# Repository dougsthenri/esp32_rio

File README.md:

# ESP32 Remote I/O

A low-cost industrial remote input/output device based on the ESP32-S3 SoC from Espressif.

## Features

* **WiFi Connectivity:** Connects to an existing WiFi network using configuration read from non-volatile storage. External antenna.
* **Digital Inputs (DI):** Ten 24 V digital, sink type, inputs.
* **Digital Outputs (DQ):** Twenty 24 V digital, sink type, outputs.
* **Output Enable (OE) Button:** A push button to globally enable/disable digital outputs.
* **Status LED:** Steady on when digital outputs are enabled. Blinks Morse code for the letter W when disconnected from WiFi network.
* **USB Console:** A command-line interface over USB Serial/JTAG for runtime configuration (e.g., WiFi setup) and debugging.
* **Reset Button:** For manually restarting the board.
* **Power Input:** 24 V, 267 mA (max.).

---
*For any issues or contributions, please refer to the project's [GitHub repository](https://github.com/dougsthenri/esp32_rio.git).*

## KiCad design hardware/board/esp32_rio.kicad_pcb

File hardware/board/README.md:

# esp32_rio
PCB project for a low-cost industrial remote I/O device based on the ESP32-S3 SoC from Espressif.
Proudly made using KiCad 9.0.

---
*For any issues or contributions, please refer to the project's [GitHub repository](https://github.com/dougsthenri/esp32_rio.git).*

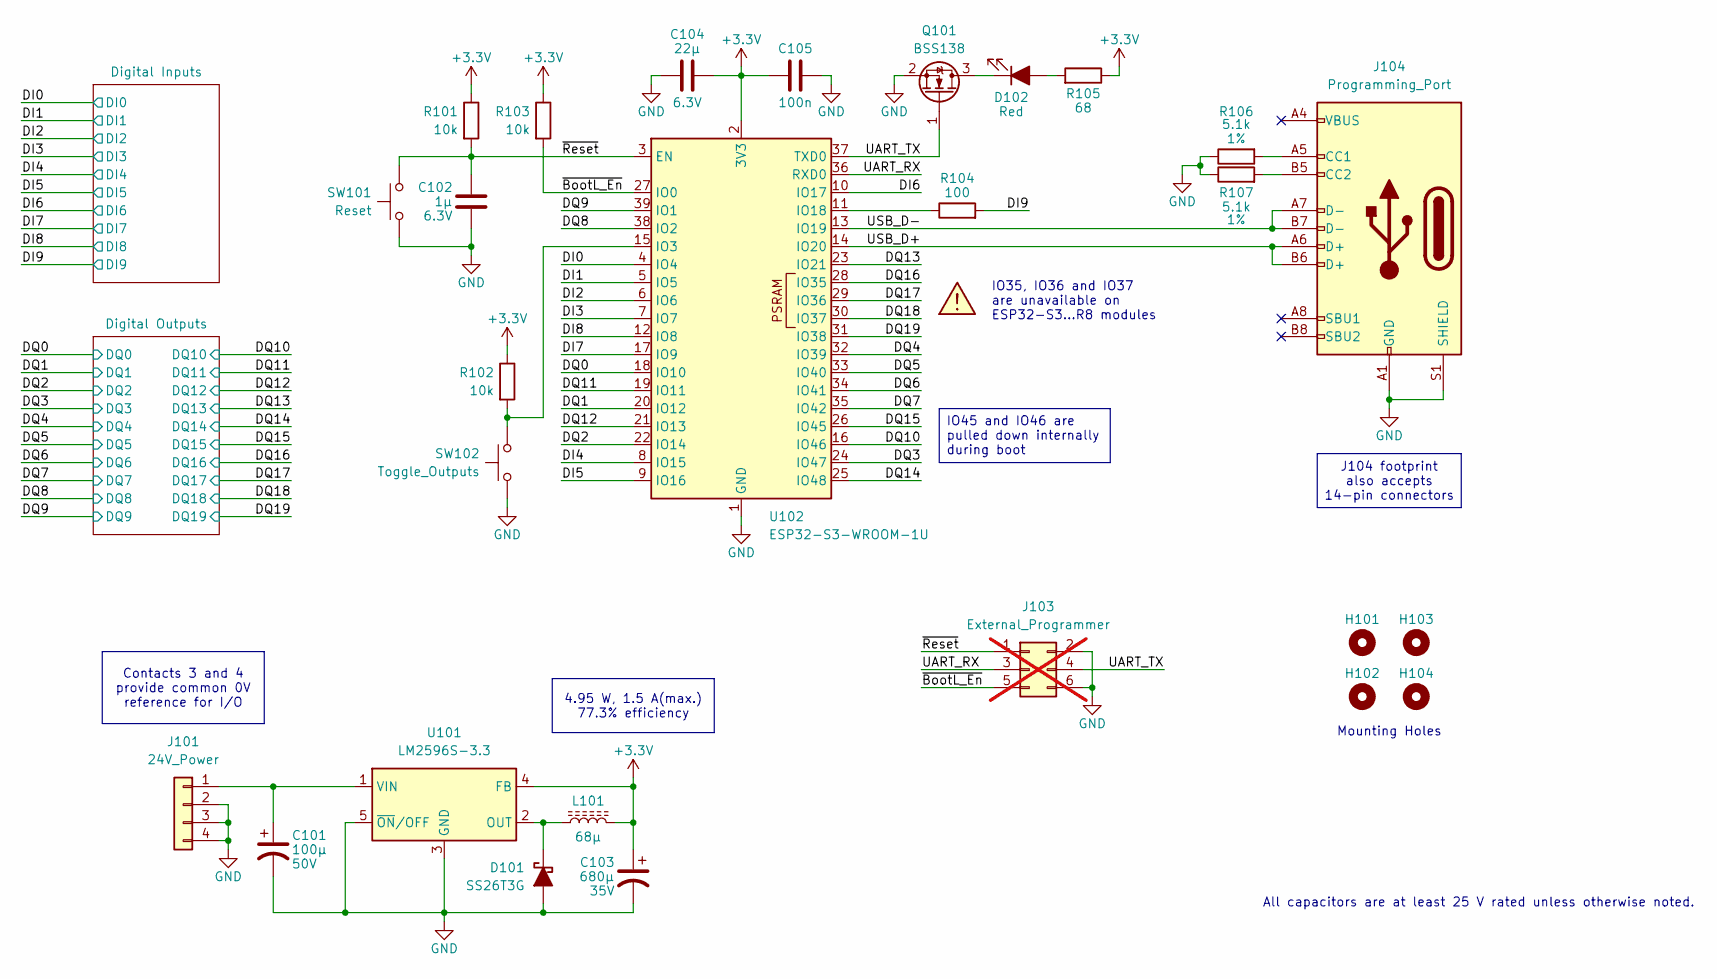
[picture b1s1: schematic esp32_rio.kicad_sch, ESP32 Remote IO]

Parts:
C101: 100µ; C_Elec_10x10.2; Voltage 50V; Part# EEHZC1H101P
C102: 1µ; C_0603_1608Metric; Voltage 6.3V; Part# CL10B105KQ8NNNC
C103: 680µ; C_Elec_10x10.2; Voltage 35V; Part# EEEFK1V331P
C104: 22µ; C_0805_2012Metric; Voltage 6.3V; Part# GRM21BZ70J226ME44L
C105: 100n; C_0603_1608Metric; Part# CC0603JRX7R9BB104
D101: SS26T3G; D_SMB; Part# SS26T3G
D102: Red; LED_Rectangular_W5.0mm_H2.0mm; Part# L-403SRD
H101, H102, H103, H104: MountingHole; MountingHole_2.1mm
J101: 24V_Power; Kefa_KF142V-5.08-4P; Part# KF142V-5.08-4P
J103: External_Programmer; PinHeader_2x03_P2.54mm_Vertical; not fitted
J104: Programming_Port; CUI_UJ20-C-V-C-3-SMT-TR; Part# GT-USB-7035D
L101: 68µ; L_Vishay_IHLP-6767; Part# IHLP6767GZER680M11
Q101: BSS138; SOT-23; Part# BSS138-7-F
R101, R102, R103: 10k; R_0603_1608Metric; Part# RC0603FR-0710KL
R104: 100; R_0603_1608Metric; Part# AC0603FR-07100RL
R105: 68; R_0603_1608Metric; Part# RC0603FR-0768RL
R106, R107: 5.1k; R_0603_1608Metric; Tolerance 1%; Part# RC0603FR-075K1L
SW101: Reset; SW_SPST_PTS645; Part# PTS645SH95SMTR92LFS
SW102: Toggle_Outputs; SW_SPST_PTS645; Part# PTS645SH95SMTR92LFS
U101: LM2596S-3.3; TO-263-5_TabPin3; Part# LM2596SX-3.3/NOPB
U102: ESP32-S3-WROOM-1U; Part# ESP32-S3-WROOM-1U-N16R2

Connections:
+3.3V: C103.1, C104.1, C105.2, L101.2, R101.1, R102.1, R103.1, R105.1, U101.4 (FB), U102.2 (3V3); also elsewhere on the board
/DI0: U102.4 (IO4); also elsewhere on the board
/DI1: U102.5 (IO5); also elsewhere on the board
/DI2: U102.6 (IO6); also elsewhere on the board
/DI3: U102.7 (IO7); also elsewhere on the board
/DI4: U102.8 (IO15); also elsewhere on the board
/DI5: U102.9 (IO16); also elsewhere on the board
/DI6: U102.10 (IO17); also elsewhere on the board
/DI7: U102.17 (IO9); also elsewhere on the board
/DI8: U102.12 (IO8); also elsewhere on the board
/DI9: R104.2; also elsewhere on the board
/DQ0: U102.18 (IO10); also elsewhere on the board
/DQ1: U102.20 (IO12); also elsewhere on the board
/DQ2: U102.22 (IO14); also elsewhere on the board
/DQ3: U102.24 (IO47); also elsewhere on the board
/DQ4: U102.32 (IO39); also elsewhere on the board
/DQ5: U102.33 (IO40); also elsewhere on the board
/DQ6: U102.34 (IO41); also elsewhere on the board
/DQ7: U102.35 (IO42); also elsewhere on the board
/DQ8: U102.38 (IO2); also elsewhere on the board
/DQ9: U102.39 (IO1); also elsewhere on the board
/DQ10: U102.16 (IO46); also elsewhere on the board
/DQ11: U102.19 (IO11); also elsewhere on the board
/DQ12: U102.21 (IO13); also elsewhere on the board
/DQ13: U102.23 (IO21); also elsewhere on the board
/DQ14: U102.25 (IO48); also elsewhere on the board
/DQ15: U102.26 (IO45); also elsewhere on the board
/DQ16: U102.28 (IO35); also elsewhere on the board
/DQ17: U102.29 (IO36); also elsewhere on the board
/DQ18: U102.30 (IO37); also elsewhere on the board
/DQ19: U102.31 (IO38); also elsewhere on the board
/UART_RX: J103.3, U102.36 (RXD0)
/UART_TX: J103.4, Q101.1 (G), U102.37 (TXD0)
/USB_D+: J104.A6 (D+), J104.B6 (D+), U102.14 (IO20)
/USB_D-: J104.A7 (D-), J104.B7 (D-), U102.13 (IO19)
/~BootL_En: J103.5, R103.2, U102.27 (IO0)
/~Reset: C102.1, J103.1, R101.2, SW101.2, U102.3 (EN)
GND: C101.2, C102.2, C103.2, C104.2, C105.1, D101.2 (A), J101.2, J101.3, J101.4, J103.2, J103.6, J104.A1 (GND), J104.A12 (GND), J104.B1 (GND), J104.B12 (GND), J104.S1 (SHIELD), Q101.2 (S), R106.1, R107.1, SW101.1, SW102.1, U101.3 (GND), U101.5 (~ON/OFF), U102.1 (GND), U102.40 (GND), U102.41 (GND); also elsewhere on the board
unnamed: D101.1 (K), L101.1, U101.2 (OUT)
unnamed: D102.2 (A), R105.2
unnamed: D102.1 (K), Q101.3 (D)
unnamed: C101.1, J101.1, U101.1 (VIN)
unnamed: J104.A5 (CC1), R106.2
unnamed: J104.B5 (CC2), R107.2
unnamed: R102.2, SW102.2, U102.15 (IO3)
unnamed: R104.1, U102.11 (IO18)

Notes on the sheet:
Mounting Holes
All capacitors are at least 25 V rated unless otherwise noted.
J104 footprint also accepts 14-pin connectors
4.95 W, 1.5 A(max.) 77.3% efficiency
IO35, IO36 and IO37 are unavailable on ESP32-S3...R8 modules
Contacts 3 and 4 provide common 0V reference for I/O
IO45 and IO46 are pulled down internally during boot

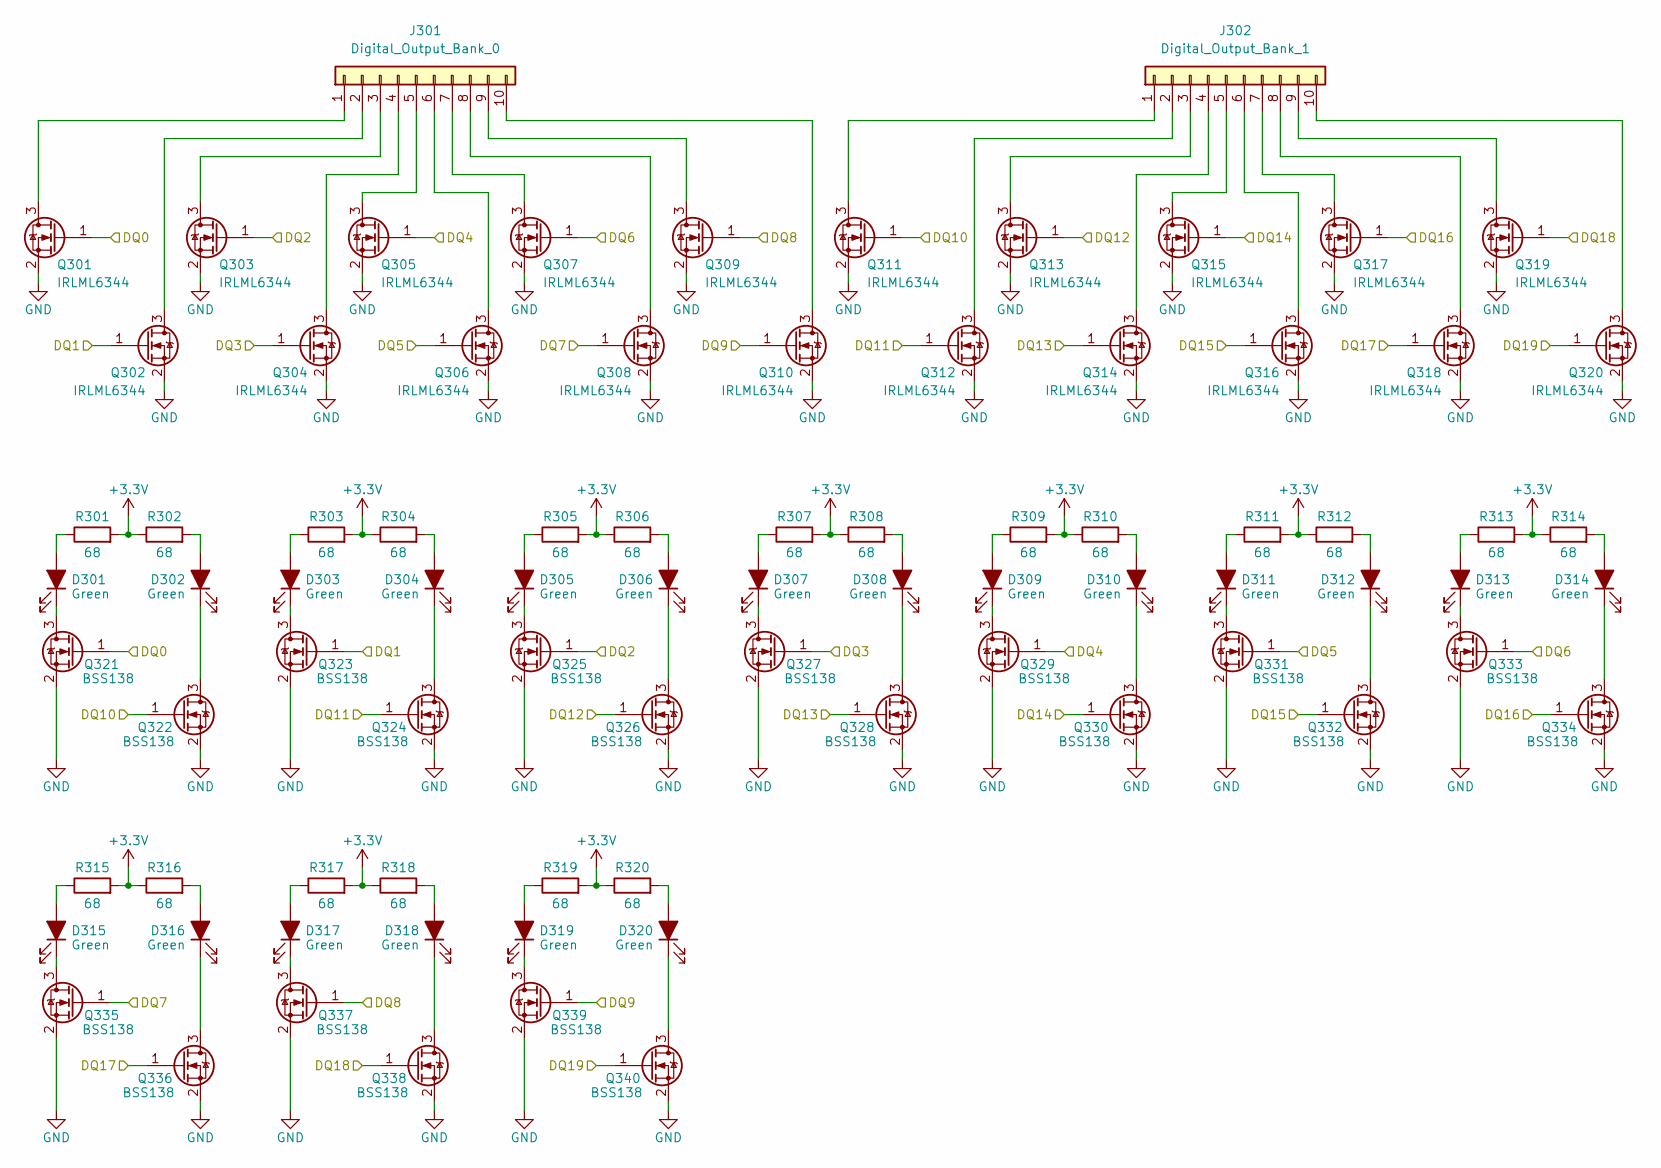
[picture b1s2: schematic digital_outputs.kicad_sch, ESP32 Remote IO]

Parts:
D301, D302, D303, D304, D305, D306, D307, D308, D309, D310, D311, D312, D313, D314, D315, D316, D317, D318, D319, D320: Green; LED_D3.0mm; Part# 204-10SYGD/S530-E2-L
J301: Digital_Output_Bank_0; Kefa_KF142V-5.08-10P; Part# KF142V-5.08-10P
J302: Digital_Output_Bank_1; Kefa_KF142V-5.08-10P; Part# KF142V-5.08-10P
Q301, Q302, Q303, Q304, Q305, Q306, Q307, Q308, Q309, Q310, Q311, Q312, Q313, Q314, Q315, Q316, Q317, Q318, Q319, Q320: IRLML6344; SOT-23; Part# IRLML6344TRPBF
Q321, Q322, Q323, Q324, Q325, Q326, Q327, Q328, Q329, Q330, Q331, Q332, Q333, Q334, Q335, Q336, Q337, Q338, Q339, Q340: BSS138; SOT-23; Part# BSS138-7-F
R301, R302, R303, R304, R305, R306, R307, R308, R309, R310, R311, R312, R313, R314, R315, R316, R317, R318, R319, R320: 68; R_0603_1608Metric; Part# RC0603FR-0768RL

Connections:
+3.3V: R301.2, R302.1, R303.2, R304.1, R305.2, R306.1, R307.2, R308.1, R309.2, R310.1, R311.2, R312.1, R313.2, R314.1, R315.2, R316.1, R317.2, R318.1, R319.2, R320.1; also elsewhere on the board
/DQ0: Q301.1 (G), Q321.1 (G); also elsewhere on the board
/DQ1: Q302.1 (G), Q323.1 (G); also elsewhere on the board
/DQ2: Q303.1 (G), Q325.1 (G); also elsewhere on the board
/DQ3: Q304.1 (G), Q327.1 (G); also elsewhere on the board
/DQ4: Q305.1 (G), Q329.1 (G); also elsewhere on the board
/DQ5: Q306.1 (G), Q331.1 (G); also elsewhere on the board
/DQ6: Q307.1 (G), Q333.1 (G); also elsewhere on the board
/DQ7: Q308.1 (G), Q335.1 (G); also elsewhere on the board
/DQ8: Q309.1 (G), Q337.1 (G); also elsewhere on the board
/DQ9: Q310.1 (G), Q339.1 (G); also elsewhere on the board
/DQ10: Q311.1 (G), Q322.1 (G); also elsewhere on the board
/DQ11: Q312.1 (G), Q324.1 (G); also elsewhere on the board
/DQ12: Q313.1 (G), Q326.1 (G); also elsewhere on the board
/DQ13: Q314.1 (G), Q328.1 (G); also elsewhere on the board
/DQ14: Q315.1 (G), Q330.1 (G); also elsewhere on the board
/DQ15: Q316.1 (G), Q332.1 (G); also elsewhere on the board
/DQ16: Q317.1 (G), Q334.1 (G); also elsewhere on the board
/DQ17: Q318.1 (G), Q336.1 (G); also elsewhere on the board
/DQ18: Q319.1 (G), Q338.1 (G); also elsewhere on the board
/DQ19: Q320.1 (G), Q340.1 (G); also elsewhere on the board
GND: Q301.2 (S), Q302.2 (S), Q303.2 (S), Q304.2 (S), Q305.2 (S), Q306.2 (S), Q307.2 (S), Q308.2 (S), Q309.2 (S), Q310.2 (S), Q311.2 (S), Q312.2 (S), Q313.2 (S), Q314.2 (S), Q315.2 (S), Q316.2 (S), Q317.2 (S), Q318.2 (S), Q319.2 (S), Q320.2 (S), Q321.2 (S), Q322.2 (S), Q323.2 (S), Q324.2 (S), Q325.2 (S), Q326.2 (S), Q327.2 (S), Q328.2 (S), Q329.2 (S), Q330.2 (S), Q331.2 (S), Q332.2 (S), Q333.2 (S), Q334.2 (S), Q335.2 (S), Q336.2 (S), Q337.2 (S), Q338.2 (S), Q339.2 (S), Q340.2 (S); also elsewhere on the board
unnamed: D301.2 (A), R301.1
unnamed: D301.1 (K), Q321.3 (D)
unnamed: D302.2 (A), R302.2
unnamed: D302.1 (K), Q322.3 (D)
unnamed: D303.2 (A), R303.1
unnamed: D303.1 (K), Q323.3 (D)
unnamed: D304.2 (A), R304.2
unnamed: D304.1 (K), Q324.3 (D)
unnamed: D305.2 (A), R305.1
unnamed: D305.1 (K), Q325.3 (D)
unnamed: D306.2 (A), R306.2
unnamed: D306.1 (K), Q326.3 (D)
unnamed: D307.2 (A), R307.1
unnamed: D307.1 (K), Q327.3 (D)
unnamed: D308.2 (A), R308.2
unnamed: D308.1 (K), Q328.3 (D)
unnamed: D309.2 (A), R309.1
unnamed: D309.1 (K), Q329.3 (D)
unnamed: D310.2 (A), R310.2
unnamed: D310.1 (K), Q330.3 (D)
unnamed: D311.2 (A), R311.1
unnamed: D311.1 (K), Q331.3 (D)
unnamed: D312.2 (A), R312.2
unnamed: D312.1 (K), Q332.3 (D)
unnamed: D313.2 (A), R313.1
unnamed: D313.1 (K), Q333.3 (D)
unnamed: D314.2 (A), R314.2
unnamed: D314.1 (K), Q334.3 (D)
unnamed: D315.2 (A), R315.1
unnamed: D315.1 (K), Q335.3 (D)
unnamed: D316.2 (A), R316.2
unnamed: D316.1 (K), Q336.3 (D)
unnamed: D317.2 (A), R317.1
unnamed: D317.1 (K), Q337.3 (D)
unnamed: D318.2 (A), R318.2
unnamed: D318.1 (K), Q338.3 (D)
unnamed: D319.2 (A), R319.1
unnamed: D319.1 (K), Q339.3 (D)
unnamed: D320.2 (A), R320.2
unnamed: D320.1 (K), Q340.3 (D)
unnamed: J301.1, Q301.3 (D)
unnamed: J301.2, Q302.3 (D)
unnamed: J301.3, Q303.3 (D)
unnamed: J301.4, Q304.3 (D)
unnamed: J301.5, Q305.3 (D)
unnamed: J301.6, Q306.3 (D)
unnamed: J301.7, Q307.3 (D)
unnamed: J301.8, Q308.3 (D)
unnamed: J301.9, Q309.3 (D)
unnamed: J301.10, Q310.3 (D)
unnamed: J302.1, Q311.3 (D)
unnamed: J302.2, Q312.3 (D)
unnamed: J302.3, Q313.3 (D)
unnamed: J302.4, Q314.3 (D)
unnamed: J302.5, Q315.3 (D)
unnamed: J302.6, Q316.3 (D)
unnamed: J302.7, Q317.3 (D)
unnamed: J302.8, Q318.3 (D)
unnamed: J302.9, Q319.3 (D)
unnamed: J302.10, Q320.3 (D)

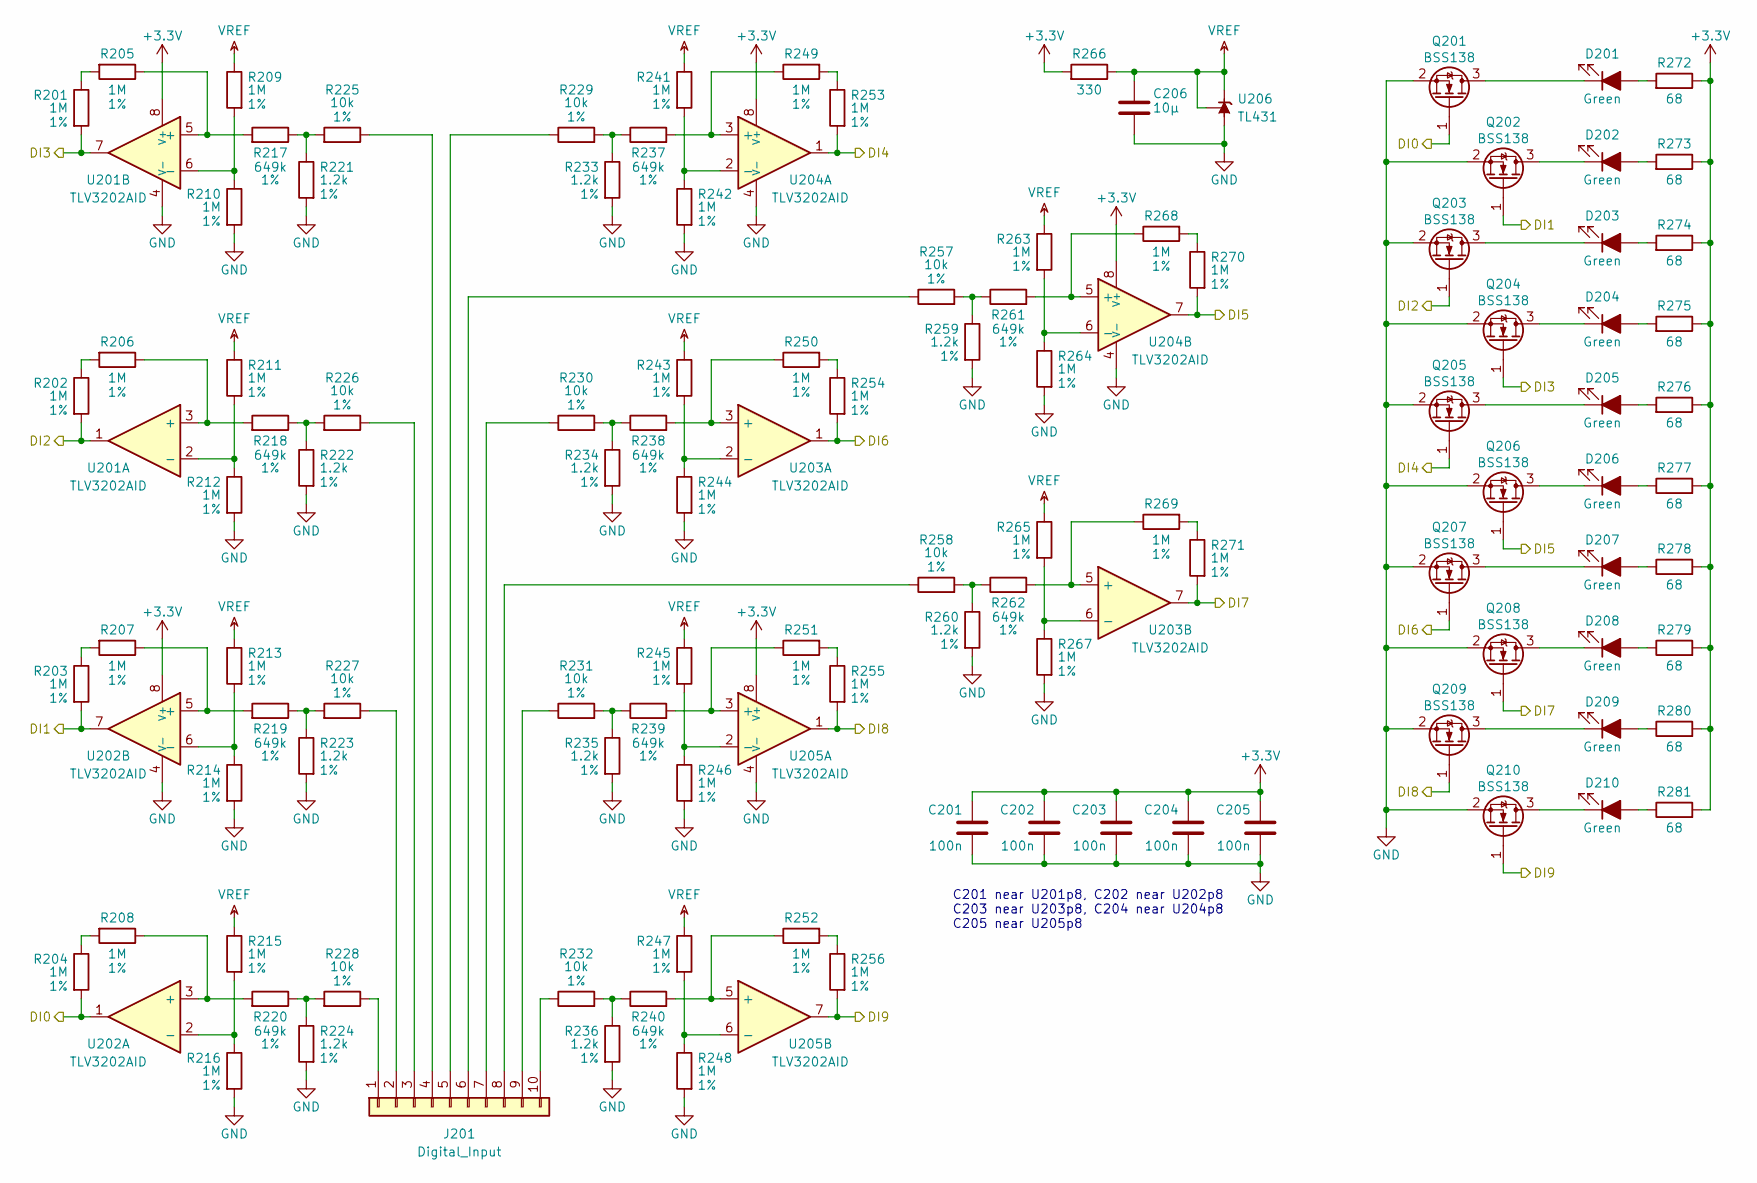
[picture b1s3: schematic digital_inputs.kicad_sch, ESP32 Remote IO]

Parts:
C201, C202, C203, C204, C205: 100n; C_0603_1608Metric; Part# CC0603JRX7R9BB104
C206: 10µ; C_0805_2012Metric; Part# CL21B106KAYQNNE
D201, D202, D203, D204, D205, D206, D207, D208, D209, D210: Green; LED_D3.0mm; Part# 204-10SYGD/S530-E2-L
J201: Digital_Input; Kefa_KF142V-5.08-10P; Part# KF142V-5.08-10P
Q201, Q202, Q203, Q204, Q205, Q206, Q207, Q208, Q209, Q210: BSS138; SOT-23; Part# BSS138-7-F
R201, R202, R203, R204, R205, R206, R207, R208, R209, R210, R211, R212, R213, R214, R215, R216, R241, R242, R243, R244, R245, R246, R247, R248, R249, R250, R251, R252, R253, R254, R255, R256, R263, R264, R265, R267, R268, R269, R270, R271: 1M; R_0603_1608Metric; Tolerance 1%; Part# RC0603FR-071ML
R217, R218, R219, R220, R237, R238, R239, R240, R261, R262: 649k; R_0603_1608Metric; Tolerance 1%; Part# RC0603FR-07649KL
R221, R222, R223, R224, R233, R234, R235, R236, R259, R260: 1.2k; R_0603_1608Metric; Tolerance 1%; Part# RC0603FR-071K2L
R225, R226, R227, R228, R229, R230, R231, R232, R257, R258: 10k; R_0603_1608Metric; Tolerance 1%; Part# RC0603FR-0710KL
R266: 330; R_0603_1608Metric; Part# RC0603FR-07330RL
R272, R273, R274, R275, R276, R277, R278, R279, R280, R281: 68; R_0603_1608Metric; Part# RC0603FR-0768RL
U201, U202, U203, U204, U205: TLV3202AID; SOIC-8_3.9x4.9mm_P1.27mm; Part# TLV3202AIDR
U206: TL431; SOT-23; Part# ZTL431AFTA

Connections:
+3.3V: C201.1, C202.1, C203.1, C204.1, C205.1, R266.2, R272.1, R273.1, R274.1, R275.1, R276.1, R277.2, R278.2, R279.2, R280.2, R281.2, U201.8 (V+), U202.8 (V+), U203.8 (V+), U204.8 (V+), U205.8 (V+); also elsewhere on the board
/DI0: Q201.1 (G), R204.2, U202.1; also elsewhere on the board
/DI1: Q202.1 (G), R203.2, U202.7; also elsewhere on the board
/DI2: Q203.1 (G), R202.2, U201.1; also elsewhere on the board
/DI3: Q204.1 (G), R201.2, U201.7; also elsewhere on the board
/DI4: Q205.1 (G), R253.2, U204.1; also elsewhere on the board
/DI5: Q206.1 (G), R270.2, U204.7; also elsewhere on the board
/DI6: Q207.1 (G), R254.2, U203.1; also elsewhere on the board
/DI7: Q208.1 (G), R271.2, U203.7; also elsewhere on the board
/DI8: Q209.1 (G), R255.2, U205.1; also elsewhere on the board
/DI9: Q210.1 (G), R256.2, U205.7; also elsewhere on the board
GND: C201.2, C202.2, C203.2, C204.2, C205.2, C206.2, Q201.2 (S), Q202.2 (S), Q203.2 (S), Q204.2 (S), Q205.2 (S), Q206.2 (S), Q207.2 (S), Q208.2 (S), Q209.2 (S), Q210.2 (S), R210.2, R212.2, R214.2, R216.2, R221.2, R222.2, R223.2, R224.2, R233.2, R234.2, R235.2, R236.2, R242.2, R244.2, R246.2, R248.2, R259.2, R260.2, R264.2, R267.2, U201.4 (V-), U202.4 (V-), U203.4 (V-), U204.4 (V-), U205.4 (V-), U206.3 (A); also elsewhere on the board
unnamed: D201.2 (A), R272.2
unnamed: D201.1 (K), Q201.3 (D)
unnamed: D202.2 (A), R273.2
unnamed: D202.1 (K), Q202.3 (D)
unnamed: D203.2 (A), R274.2
unnamed: D203.1 (K), Q203.3 (D)
unnamed: D204.2 (A), R275.2
unnamed: D204.1 (K), Q204.3 (D)
unnamed: D205.2 (A), R276.2
unnamed: D205.1 (K), Q205.3 (D)
unnamed: D206.2 (A), R277.1
unnamed: D206.1 (K), Q206.3 (D)
unnamed: D207.2 (A), R278.1
unnamed: D207.1 (K), Q207.3 (D)
unnamed: D208.2 (A), R279.1
unnamed: D208.1 (K), Q208.3 (D)
unnamed: D209.2 (A), R280.1
unnamed: D209.1 (K), Q209.3 (D)
unnamed: D210.2 (A), R281.1
unnamed: D210.1 (K), Q210.3 (D)
unnamed: J201.1, R228.1
unnamed: J201.2, R227.1
unnamed: J201.3, R226.1
unnamed: J201.4, R225.1
unnamed: J201.5, R229.1
unnamed: J201.6, R257.1
unnamed: J201.7, R230.1
unnamed: J201.8, R258.1
unnamed: J201.9, R231.1
unnamed: J201.10, R232.1
unnamed: R201.1, R205.2
unnamed: R202.1, R206.2
unnamed: R203.1, R207.2
unnamed: R204.1, R208.2
unnamed: R217.1, R221.1, R225.2
unnamed: R218.1, R222.1, R226.2
unnamed: R219.1, R223.1, R227.2
unnamed: R220.1, R224.1, R228.2
unnamed: R229.2, R233.1, R237.1
unnamed: R230.2, R234.1, R238.1
unnamed: R231.2, R235.1, R239.1
unnamed: R232.2, R236.1, R240.1
unnamed: R249.2, R253.1
unnamed: R250.2, R254.1
unnamed: R251.2, R255.1
unnamed: R252.2, R256.1
unnamed: R257.2, R259.1, R261.1
unnamed: R258.2, R260.1, R262.1
unnamed: R268.2, R270.1
unnamed: R269.2, R271.1
unnamed: R206.1, R218.2, U201.3 (+)
unnamed: R211.2, R212.1, U201.2 (-)
unnamed: R205.1, R217.2, U201.5 (+)
unnamed: R209.2, R210.1, U201.6 (-)
unnamed: R208.1, R220.2, U202.3 (+)
unnamed: R215.2, R216.1, U202.2 (-)
unnamed: R207.1, R219.2, U202.5 (+)
unnamed: R213.2, R214.1, U202.6 (-)
unnamed: R238.2, R250.1, U203.3 (+)
unnamed: R243.2, R244.1, U203.2 (-)
unnamed: R262.2, R269.1, U203.5 (+)
unnamed: R265.2, R267.1, U203.6 (-)
unnamed: R237.2, R249.1, U204.3 (+)
unnamed: R241.2, R242.1, U204.2 (-)
unnamed: R261.2, R268.1, U204.5 (+)
unnamed: R263.2, R264.1, U204.6 (-)
unnamed: R239.2, R251.1, U205.3 (+)
unnamed: R245.2, R246.1, U205.2 (-)
unnamed: R240.2, R252.1, U205.5 (+)
unnamed: R247.2, R248.1, U205.6 (-)
VREF: C206.1, R209.1, R211.1, R213.1, R215.1, R241.1, R243.1, R245.1, R247.1, R263.1, R265.1, R266.1, U206.1 (K), U206.2 (REF)

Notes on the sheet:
C201 near U201p8, C202 near U202p8 C203 near U203p8, C204 near U204p8 C205 near U205p8

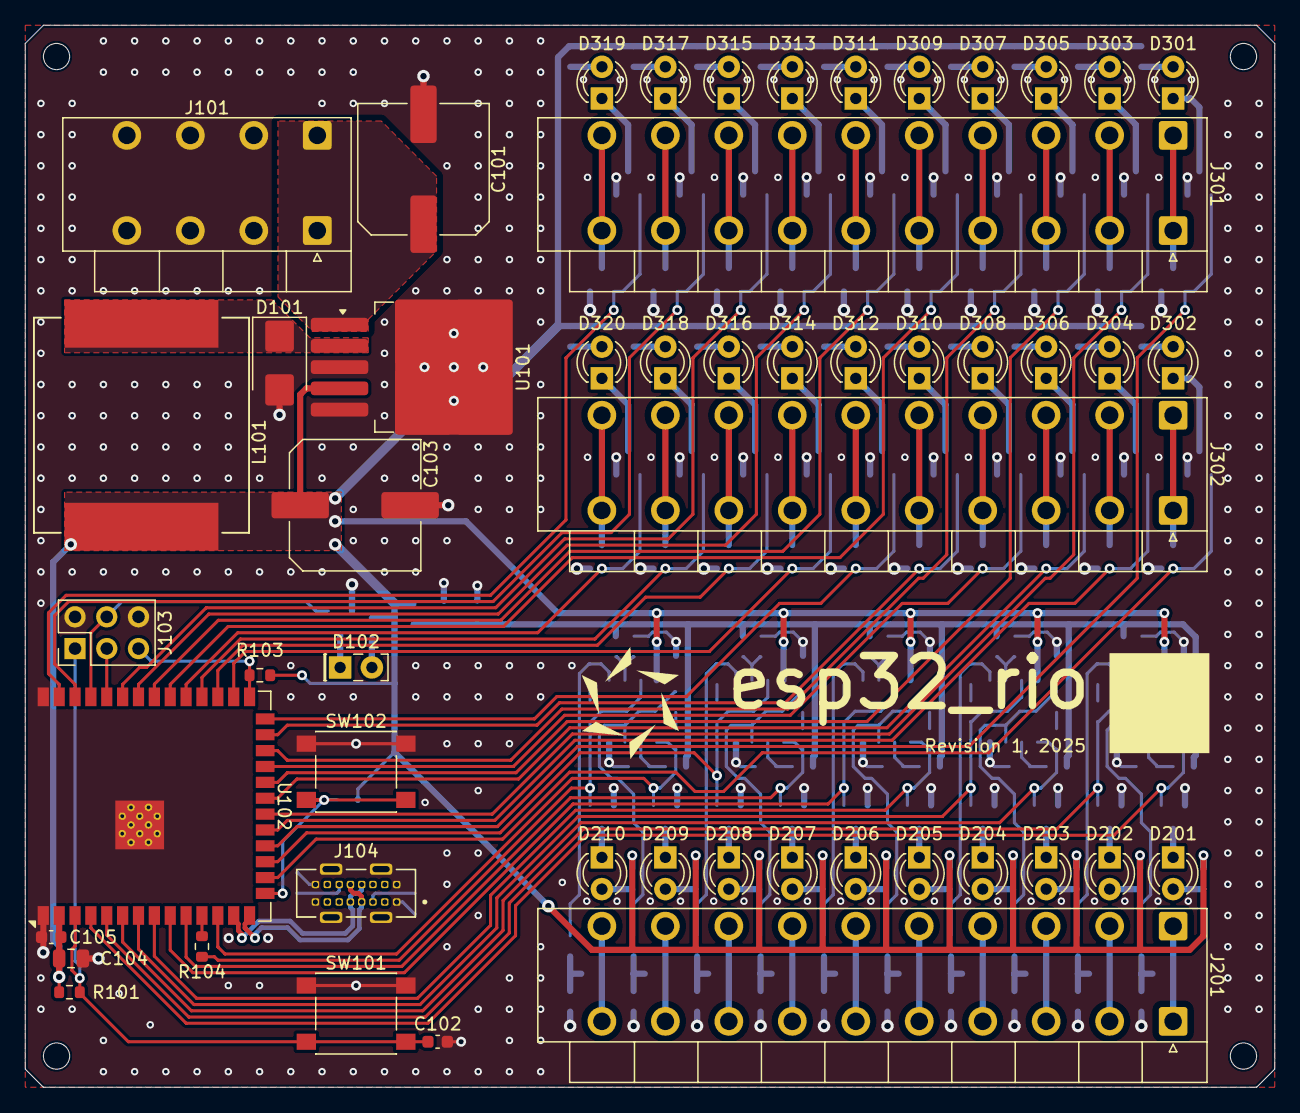
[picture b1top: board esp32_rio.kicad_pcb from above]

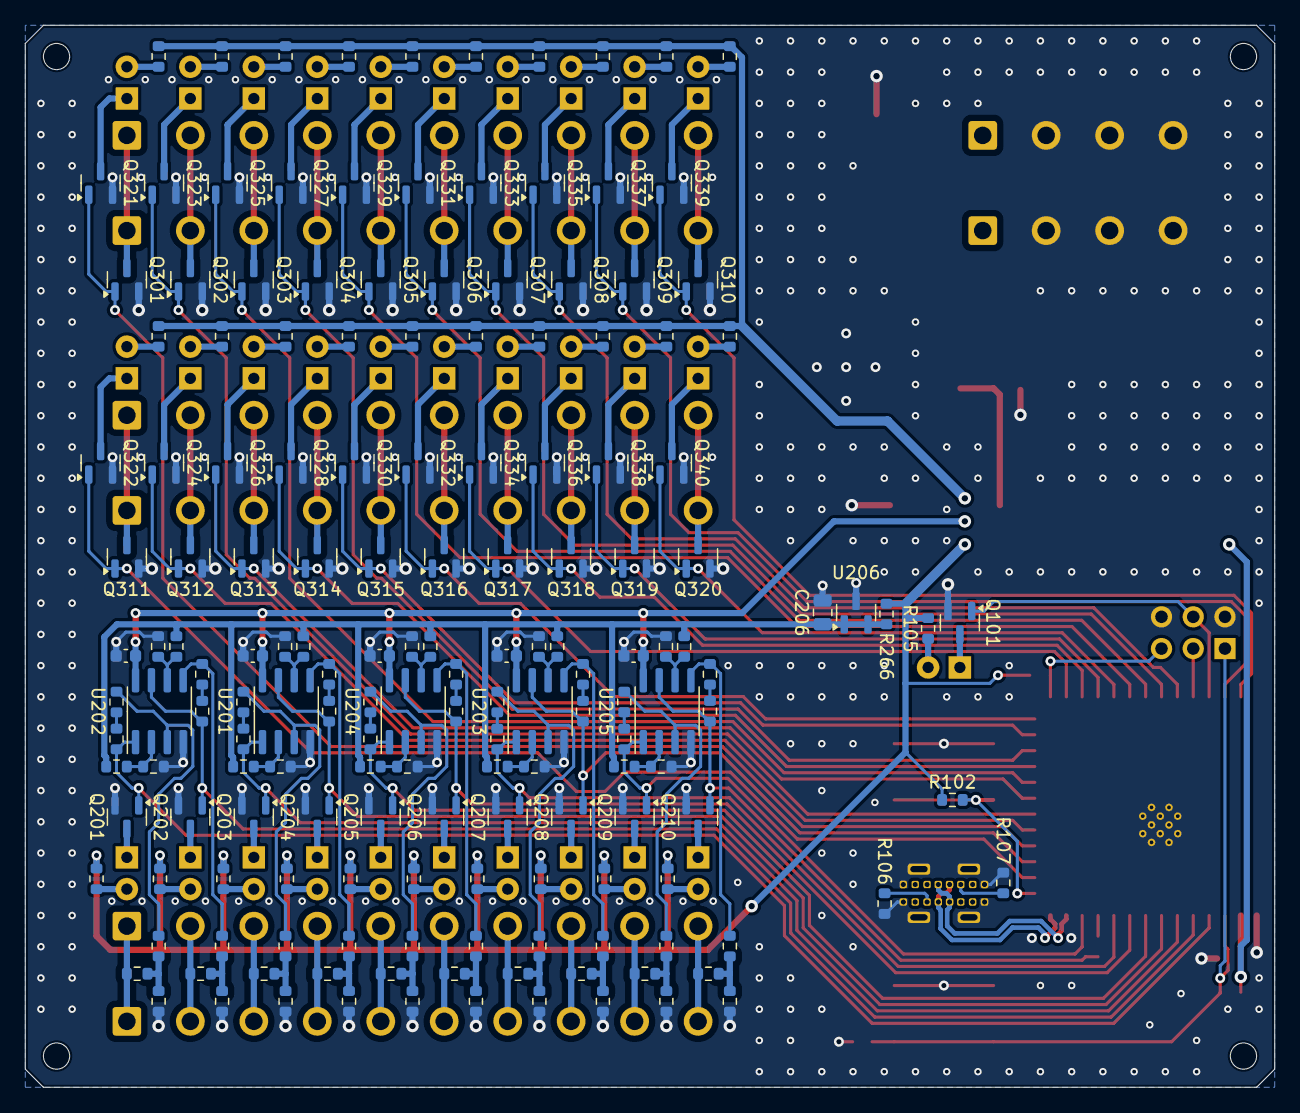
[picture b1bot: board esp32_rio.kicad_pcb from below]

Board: 2 copper layers, 100.0 x 85.0 mm, 223 parts (168 on the bottom side), 177 nets.

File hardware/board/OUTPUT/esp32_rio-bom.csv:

"Reference","Value","Qty","DNP","Part#","Tolerance","Voltage"
"C101","100µ","1","","EEHZC1H101P","","50V"
"C102","1µ","1","","CL10B105KQ8NNNC","","6.3V"
"C103","680µ","1","","EEEFK1V331P","","35V"
"C104","22µ","1","","GRM21BZ70J226ME44L","","6.3V"
"C105,C201,C202,C203,C204,C205","100n","6","","CC0603JRX7R9BB104","",""
"C206","10µ","1","","CL21B106KAYQNNE","",""
"D101","SS26T3G","1","","SS26T3G","",""
"D102","Red","1","","L-403SRD","",""
"D201,D202,D203,D204,D205,D206,D207,D208,D209,D210,D301,D302,D303,D304,D305,D306,D307,D308,D309,D310,D311,D312,D313,D314,D315,D316,D317,D318,D319,D320","Green","30","","204-10SYGD/S530-E2-L","",""
"J101","24V_Power","1","","KF142V-5.08-4P","",""
"J103","External_Programmer","1","DNP","","",""
"J104","Programming_Port","1","","GT-USB-7035D","",""
"J201","Digital_Input","1","","KF142V-5.08-10P","",""
"J301","Digital_Output_Bank_0","1","","KF142V-5.08-10P","",""
"J302","Digital_Output_Bank_1","1","","KF142V-5.08-10P","",""
"L101","68µ","1","","IHLP6767GZER680M11","",""
"Q101,Q201,Q202,Q203,Q204,Q205,Q206,Q207,Q208,Q209,Q210,Q321,Q322,Q323,Q324,Q325,Q326,Q327,Q328,Q329,Q330,Q331,Q332,Q333,Q334,Q335,Q336,Q337,Q338,Q339,Q340","BSS138","31","","BSS138-7-F","",""
"Q301,Q302,Q303,Q304,Q305,Q306,Q307,Q308,Q309,Q310,Q311,Q312,Q313,Q314,Q315,Q316,Q317,Q318,Q319,Q320","IRLML6344","20","","IRLML6344TRPBF","",""
"R101,R102,R103","10k","3","","RC0603FR-0710KL","",""
"R104","100","1","","AC0603FR-07100RL","",""
"R105,R272,R273,R274,R275,R276,R277,R278,R279,R280,R281,R301,R302,R303,R304,R305,R306,R307,R308,R309,R310,R311,R312,R313,R314,R315,R316,R317,R318,R319,R320","68","31","","RC0603FR-0768RL","",""
"R106,R107","5.1k","2","","RC0603FR-075K1L","1%",""
"R201,R202,R203,R204,R205,R206,R207,R208,R209,R210,R211,R212,R213,R214,R215,R216,R241,R242,R243,R244,R245,R246,R247,R248,R249,R250,R251,R252,R253,R254,R255,R256,R263,R264,R265,R267,R268,R269,R270,R271","1M","40","","RC0603FR-071ML","1%",""
"R217,R218,R219,R220,R237,R238,R239,R240,R261,R262","649k","10","","RC0603FR-07649KL","1%",""
"R221,R222,R223,R224,R233,R234,R235,R236,R259,R260","1.2k","10","","RC0603FR-071K2L","1%",""
"R225,R226,R227,R228,R229,R230,R231,R232,R257,R258","10k","10","","RC0603FR-0710KL","1%",""
"R266","330","1","","RC0603FR-07330RL","",""
"SW101","Reset","1","","PTS645SH95SMTR92LFS","",""
"SW102","Toggle_Outputs","1","","PTS645SH95SMTR92LFS","",""
"U101","LM2596S-3.3","1","","LM2596SX-3.3/NOPB","",""
"U102","ESP32-S3-WROOM-1U","1","","ESP32-S3-WROOM-1U-N16R2","",""
"U201,U202,U203,U204,U205","TLV3202AID","5","","TLV3202AIDR","",""
"U206","TL431","1","","ZTL431AFTA","",""

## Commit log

2025-06-07 Added installation photo
2025-06-09 Added Bill of Materials file
